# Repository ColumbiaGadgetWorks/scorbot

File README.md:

# Scorbot ER-4u ESP32 controller

A replacement controller for the Intelitek Scorbot ER-4u robot arm. An ESP32
drives the arm's six DC motors and reads its encoders and home switches. A web
UI (WiFi, with an access-point fallback) gives jogging, a live 3D view,
self-tests, homing and travel calibration, and there is a JSON HTTP/WebSocket
API.

| Folder | What's in it |
| --- | --- |
| [`hardware/scorbot-controller/`](hardware/scorbot-controller/) | KiCad 7 project for the master board, generated from Python (`generator/design.py`), autorouted, with JLCPCB fab files in `fab/` |
| [`firmware/`](firmware/) | ESP-IDF 5.3+ firmware, the single-file web UI, and host-side tests on a simulated arm |
| [`flasher/`](flasher/) | Guided web firmware installer: open <https://columbiagadgetworks.github.io/scorbot/> in Chrome or Edge and flash over USB |

The board takes an ESP32-DevKitC (WROOM-32D or -32E), six motor driver
carriers and a DROK 5 V buck module on headers. The carriers are the DRV8874
board in [`hardware/drv8874-carrier/`](hardware/drv8874-carrier/), or
Pololu's #4035 (DRV8874) or #4036 (DRV8876), picked with one menuconfig
setting in the firmware. The
robot's DB-50 cable plugs straight in. JLCPCB places the SMD parts (passives,
LEDs, the TCA9555 I/O expander and two ADS1115 ADCs); the connectors, sockets
and big capacitors are through-hole and hand-soldered.

**Status:** the board has not been ordered or tested, and the firmware has not run on
hardware. Read "Must check before ordering boards" in the
[hardware README](hardware/scorbot-controller/README.md) before ordering.

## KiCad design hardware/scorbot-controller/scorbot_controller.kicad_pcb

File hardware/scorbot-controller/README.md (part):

# Scorbot ER-4u ESP32 master board (KiCad)

KiCad project for the replacement controller: an ESP32 DevKit, six Pololu
DRV8874 carriers and a DROK mini 5 V buck module plug into a master board,
and the robot's DD-50 cable plugs straight into the board edge. JLCPCB
places the SMD parts: passives, LEDs, the SS14, the TCA9555 I/O expander and
two ADS1115 ADCs.

**Status: v0.4, generated: schematic complete, carrier and DD-50 footprints checked against their datasheets, PCB autorouted. Ready to order; check part orientation in JLC's preview.**

| File | What it is |
| --- | --- |
| `scorbot_controller.kicad_pro/.kicad_sch/.kicad_pcb` | The KiCad project (opens in KiCad 7, 8 or 9) |
| `lib/Scorbot.kicad_sym`, `lib/Scorbot.pretty/` | Custom parts: DevKit socket, DRV8874 carrier socket, DD-50 female R/A |
| `docs/schematic.pdf`, `docs/pcb_placement.png`, `docs/pcb_routed_F.png`, `docs/pcb_routed_B.png` | Previews (B side is mirrored) |
| `bom.csv` | Grouped BOM |
| `generator/design.py` | **Single source of truth**: every part, footprint, pin-to-net map and placement |
| `generate.sh` | Regenerates everything from `design.py`, then checks it |

## Regenerating

```sh
pip install kiutils cairosvg   # plus KiCad 7+ (kicad-cli and its pcbnew Python module)
# optional autorouting: Java 17+, xvfb-run and the Freerouting 1.9.0 jar
# (https://github.com/freerouting/freerouting/releases/tag/v1.9.0)
FREEROUTING_JAR=/path/freerouting-1.9.0.jar ./generate.sh
```

Routing takes about 3 minutes. `gen_route.py` retries up to `FREEROUTING_TRIES`
times (default 3) because Freerouting's result varies between runs, and it
keeps the run with the fewest unconnected items.

`generate.sh` writes the library, schematic, PCB and BOM, then:

- exports KiCad's own netlist from the schematic and checks it against
  `design.py` pin by pin (currently 354 connections, 0 mismatches);
- runs KiCad DRC on the board. Current result: 0 unconnected items, 0
  clearance or courtyard errors, and a few silkscreen and thermal-relief
  warnings. `lib_footprint_issues` only appears when the
  standard KiCad libraries aren't in the global library table.

Editing the `.kicad_sch` / `.kicad_pcb` by hand is fine once you take over
the design; just stop running the generator after that, or it overwrites your
changes.

## Must check before ordering boards

Done:

- **Pololu carrier pinout** is taken from Pololu's labeled top view: left
  row VM, GND, EN, PH, PMODE, SLEEP, VREF; right row VIN, GND, OUT1, OUT2,
  IMODE, FAULT, CS; rows 0.5" apart. Silkscreen marks VM (top left) and VIN
  (top right) on each socket: plug the carrier in components-up with its VM
  pin at the VM mark.
- **DevKit pinout** matches a photo of the board in hand (DevKitC V4 layout,
  3V3 at the antenna end).
- **Copper**: 1 oz. VIN/VM traces are 2.5 mm with 1.6/0.8 mm vias, motor
  traces 1.2 mm with 1.2/0.6 mm vias.
- **DevKit row spacing** confirmed at 1.0" (25.4 mm).
- **DD-50 footprint** follows Amphenol's D-Sub brochure for DD50S564TLF
  (stamped contacts, termination type 5): tail rows 2.54 mm apart, the row
  nearest the flange 10.40 mm from it, 2.77 mm pitch, 61.11 mm between the
  shell holes.
- **LCSC numbers** checked by search (C465732 is TI's TCA9555PWR; its LCSC
  attribute text is a generic I/O-expander template).

Still to check:

1. **DD-50 bracket holes** (not blocking): the brochure doesn't dimension
   the 50-way plastic bracket, so the two 3.2 mm holes sit on the shell-hole
   centres (61.11 mm apart), 12.94 mm behind the flange. The connector is
   held by its 50 soldered pins either way.
2. **R31-R36 LCSC number**: C341654 (Fenghua 47 R 2512 1 W, Extended;
   alternate C4347277). Confirm stock.
3. **Part orientation in JLC's placement preview** (see below). First pass
   checked: the TSSOPs were 90 degrees off and are now corrected in the CPL;
   D5 and the LEDs were already right. Re-check U5-U7 after re-uploading.
4. **Autorouted copper.** DRC-clean but not pretty; look over the VIN/VM
   and MOT paths, and the long parallel runs across the middle.
5. **Screw terminal wire entry** (J2, J3, J7) should face the board edge.
   Check in KiCad's 3D viewer.

Fit by hand, one of each pair:

- **D1 (SMBJ18A, SMB) or D8 (1.5KE18A / P6KE18A, through-hole)**: the
  reverse-polarity / over-voltage clamp. Neither is placed by JLC.
- **F1 (blade fuse holder) or J7 (screw terminal + inline fuse)**.
- **J1 (barrel jack) or J2 (screw terminal)** for the 12 V input.

## Silkscreen

`generator/gen_silk.py` runs after routing and adds front labels without
touching copper:

- **Power:** 12V IN (barrel, centre +, 18 V max), 12V IN 2 (+/-), both fuse
  options (5 A blade F1, inline-fuse terminal J7: fit one), E-STOP (NC), and
  "TVS: fit D1 OR D8".
- **Buck module:** "12V -> 5V BUCK, set to 5.0 V before fitting the ESP32",
  and each pin: IN+ 12V, IN- GND, OUT- GND, OUT+ 5V.
- **Headers:** I2C (3V3 GND SDA SCL) and GPIO from the TCA9555 (P06 P07 P17
  GND), each pin named.
- **ESP32 DevKit:** USB-end arrow; 5V, 3V3 and GND turned and moved inward,
  off the board edge and clear of the pins.
- **Driver sockets:** M1-M6 with their joints (BASE, SHOULDER, ELBOW,
  WRIST A, WRIST B, GRIPPER) inside each outline.
- **Status LEDs:** VM, 5V, STATUS, 3V3.
- **DB-50:** ROBOT CABLE / DD-50.
- **CGW logo:** 23 mm tall, bottom middle.

Edit `LABELS`, `LOGO` and `LOGO_H` in `gen_silk.py` to change them.

Logo art: `art/columbia_gadget_works_logo.png` (front, placed by
`gen_silk.py`) and `art/stealie.png` (back, `LOGO_BACK` in `gen_pcb.py`)
become filled silkscreen through `generator/silk_art.py`. Silkscreen is one
colour: every non-white area of the image prints.

## Ordering at JLCPCB

`generator/gen_fab.py` (run by `generate.sh`) writes `fab/`:

- `scorbot_controller_gerbers.zip`: upload as the PCB (2 layers, 1.6 mm,
  1 oz copper).
- `jlc_bom.csv` and `jlc_cpl.csv`: upload for PCB Assembly, top side only.
  These list only the SMD parts JLC places. Everything else is
  hand-soldered: see the buy list in the plan doc.

### Checking the JLC part numbers

For each line of `fab/jlc_bom.csv`, search the LCSC number at
<https://jlcpcb.com/parts> and confirm:

- value and package match the Comment and Footprint columns (0805, 1206,
  SMA, TSSOP-24, MSOP/VSSOP-10);
- capacitors are X7R/X5R and 25 V or more; R31-R36 are 47 R, 2512, 1 W
  (they dissipate about 0.3 W each);
- Basic vs Extended (each Extended part adds a one-off loading fee, about
  $1.50-3);
- stock covers (quantity x number of boards).

If a number is wrong or out of stock, pick any equivalent Basic part and
change it in the `LCSC` table in `generator/gen_fab.py` (or edit the CSV).

### Checking orientation in JLC's placement preview

After uploading the BOM and CPL, JLC shows each part on the board. Zoom in
and check:

- **U5 (TCA9555), U6/U7 (ADS1115)**: the pin-1 dot on the chip sits on the
  pin-1 marker of the footprint.
- **D5 (SS14)**: the cathode band is on the pad marked as cathode (toward
  the DevKit's 5 V feed).
- **LEDs D3, D4, D6, D7** (green, green, red, green): the cathode mark
  faces the GND side.
- Resistors and capacitors have no polarity.

If a part is turned the wrong way, rotate it in JLC's tool (or add 90/180 to
its Rotation in `jlc_cpl.csv`). To make the fix permanent, add the
footprint to `ROT_FIX` in `generator/gen_fab.py`. It already turns the TSSOPs
(U5-U7) by -90 degrees, because JLC's TSSOP models sit 90 degrees from KiCad's.

## Design notes

- **DB50 pinout**: SCORBOT-ER 4u User Manual, Chapter 8 (identical to the
  ER III manual Table D-1). Pins 37-44 unused; pin 22 (gripper switch) has no
  connection in the arm. Motor +/- labels differ between manuals; firmware
  sets direction.
- **Encoders**: bare IR LEDs + phototransistors. 47 R per axis from 5 V for
  VLED (ER III reference value; check against the ER-4u's upgraded PC510
  encoders). P0/P1 have 4.7 k pull-ups to 3.3 V and 1 nF, straight into the
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
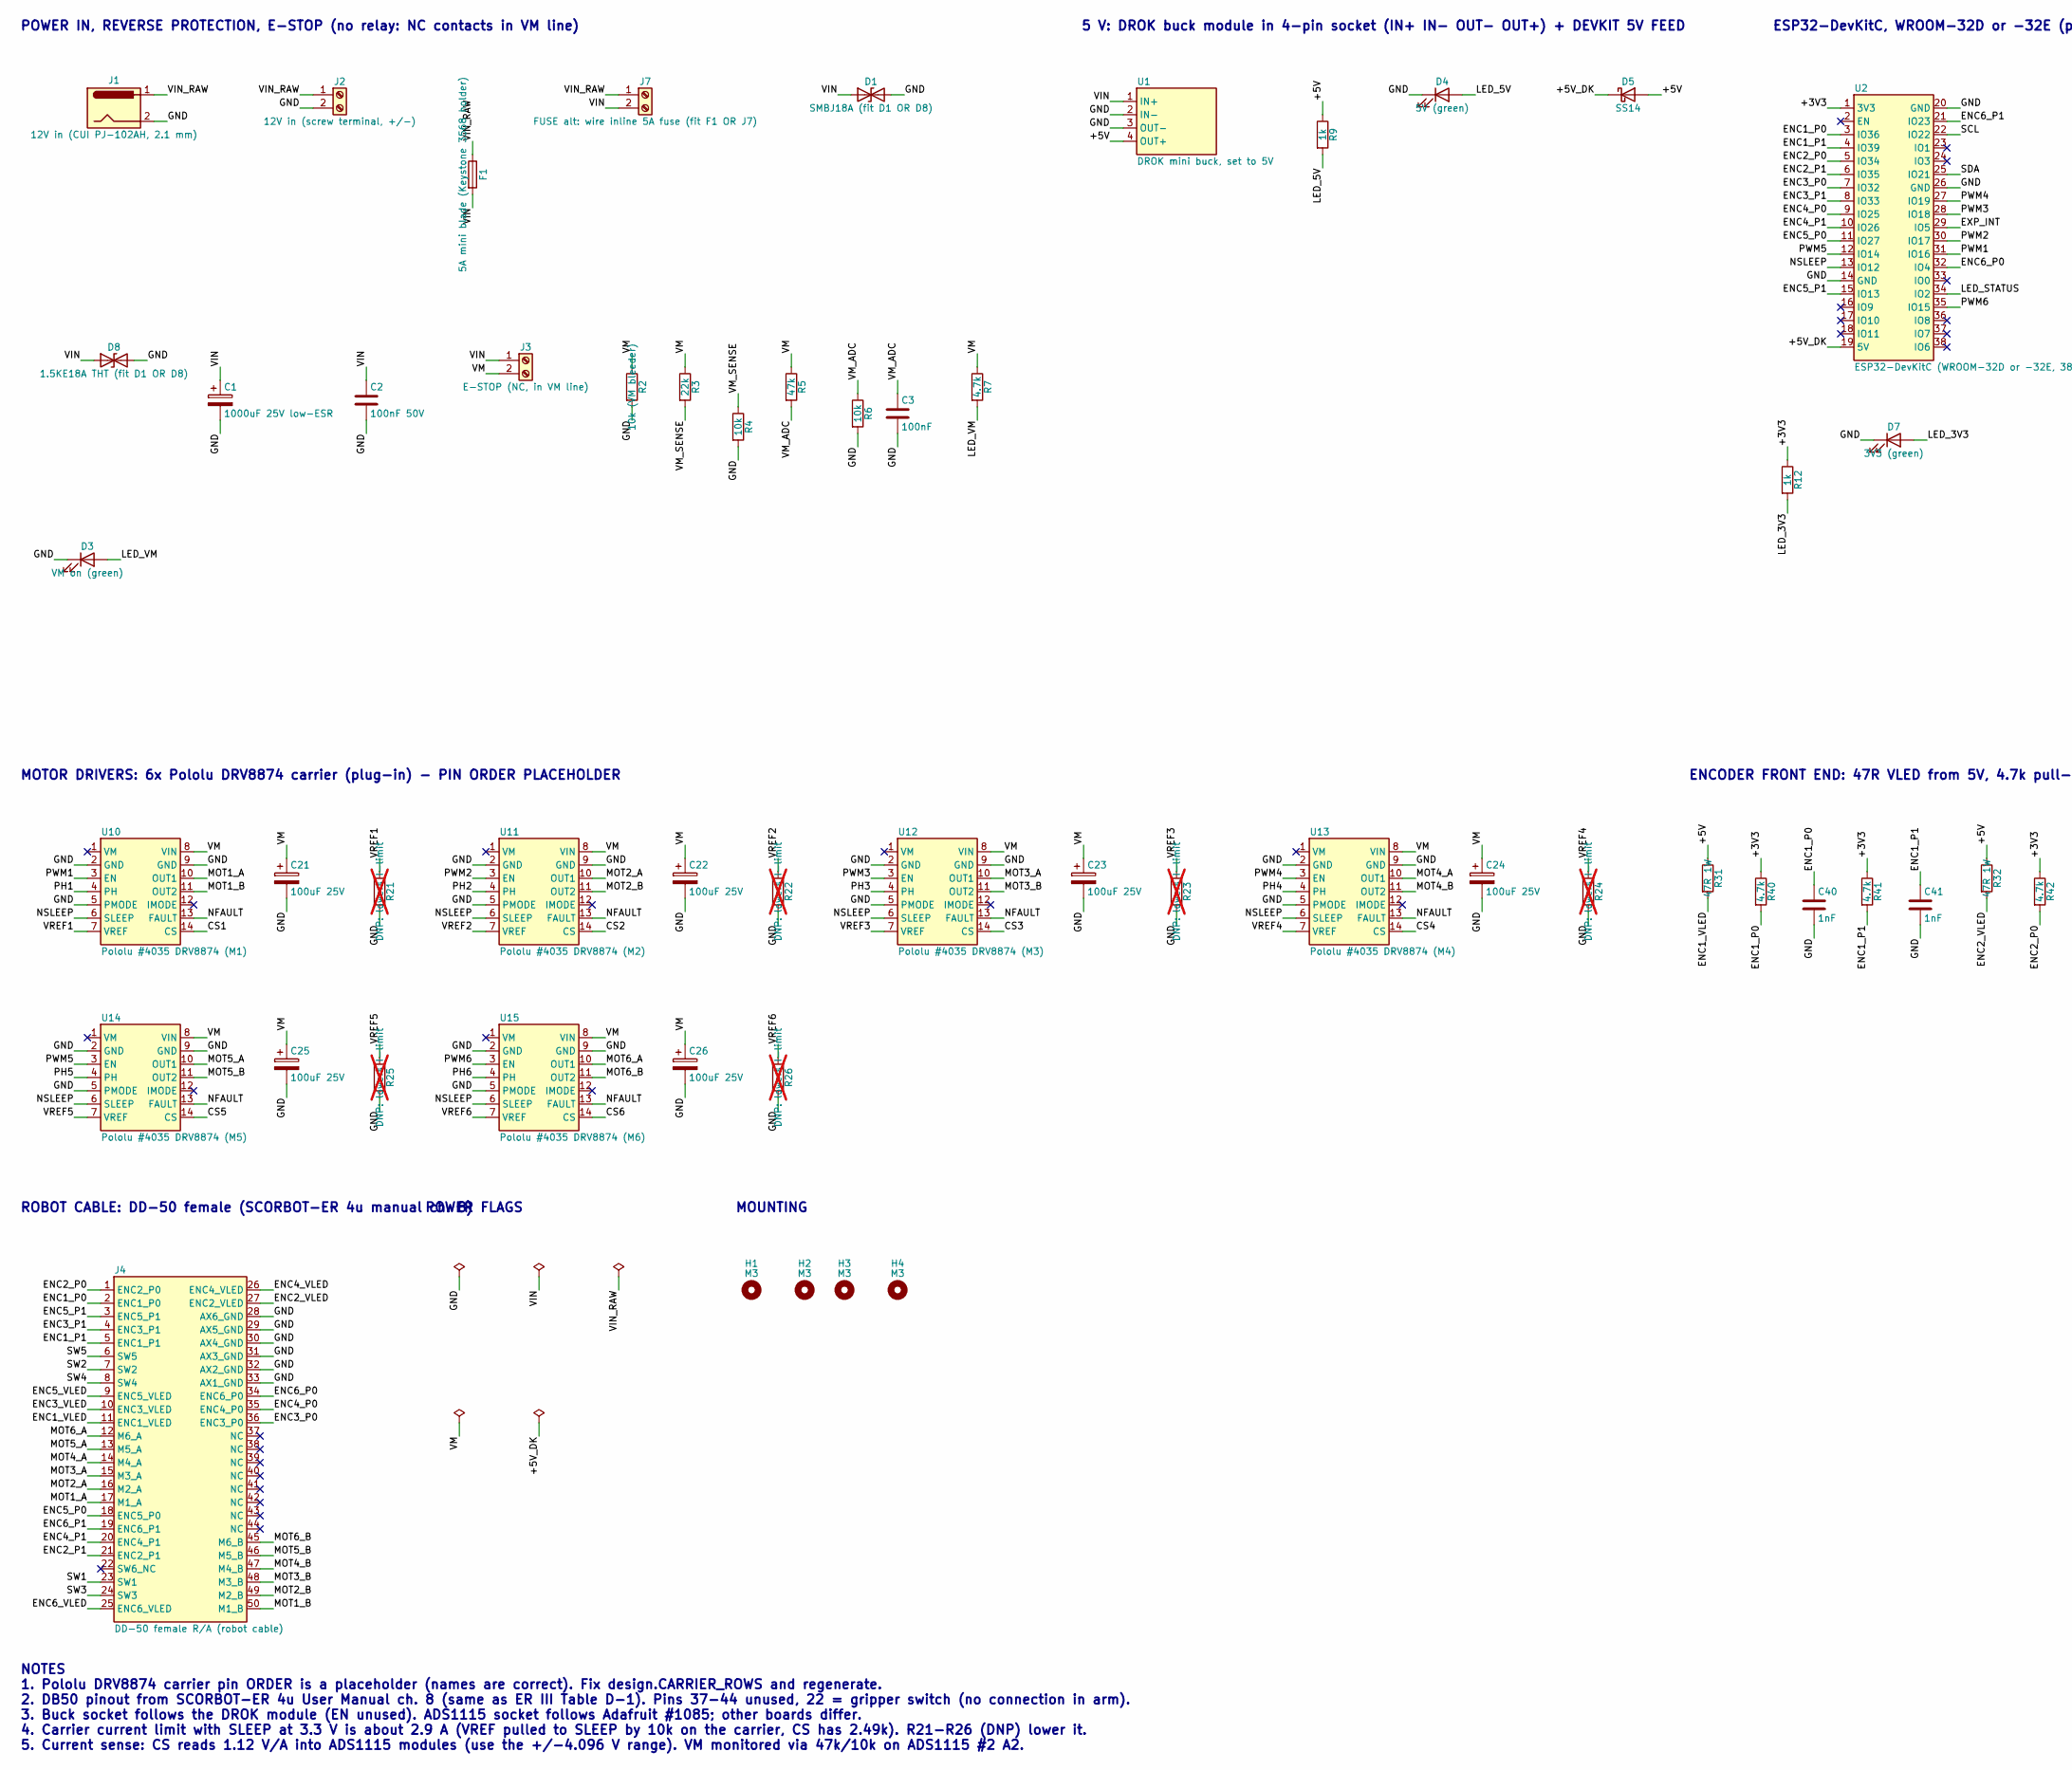
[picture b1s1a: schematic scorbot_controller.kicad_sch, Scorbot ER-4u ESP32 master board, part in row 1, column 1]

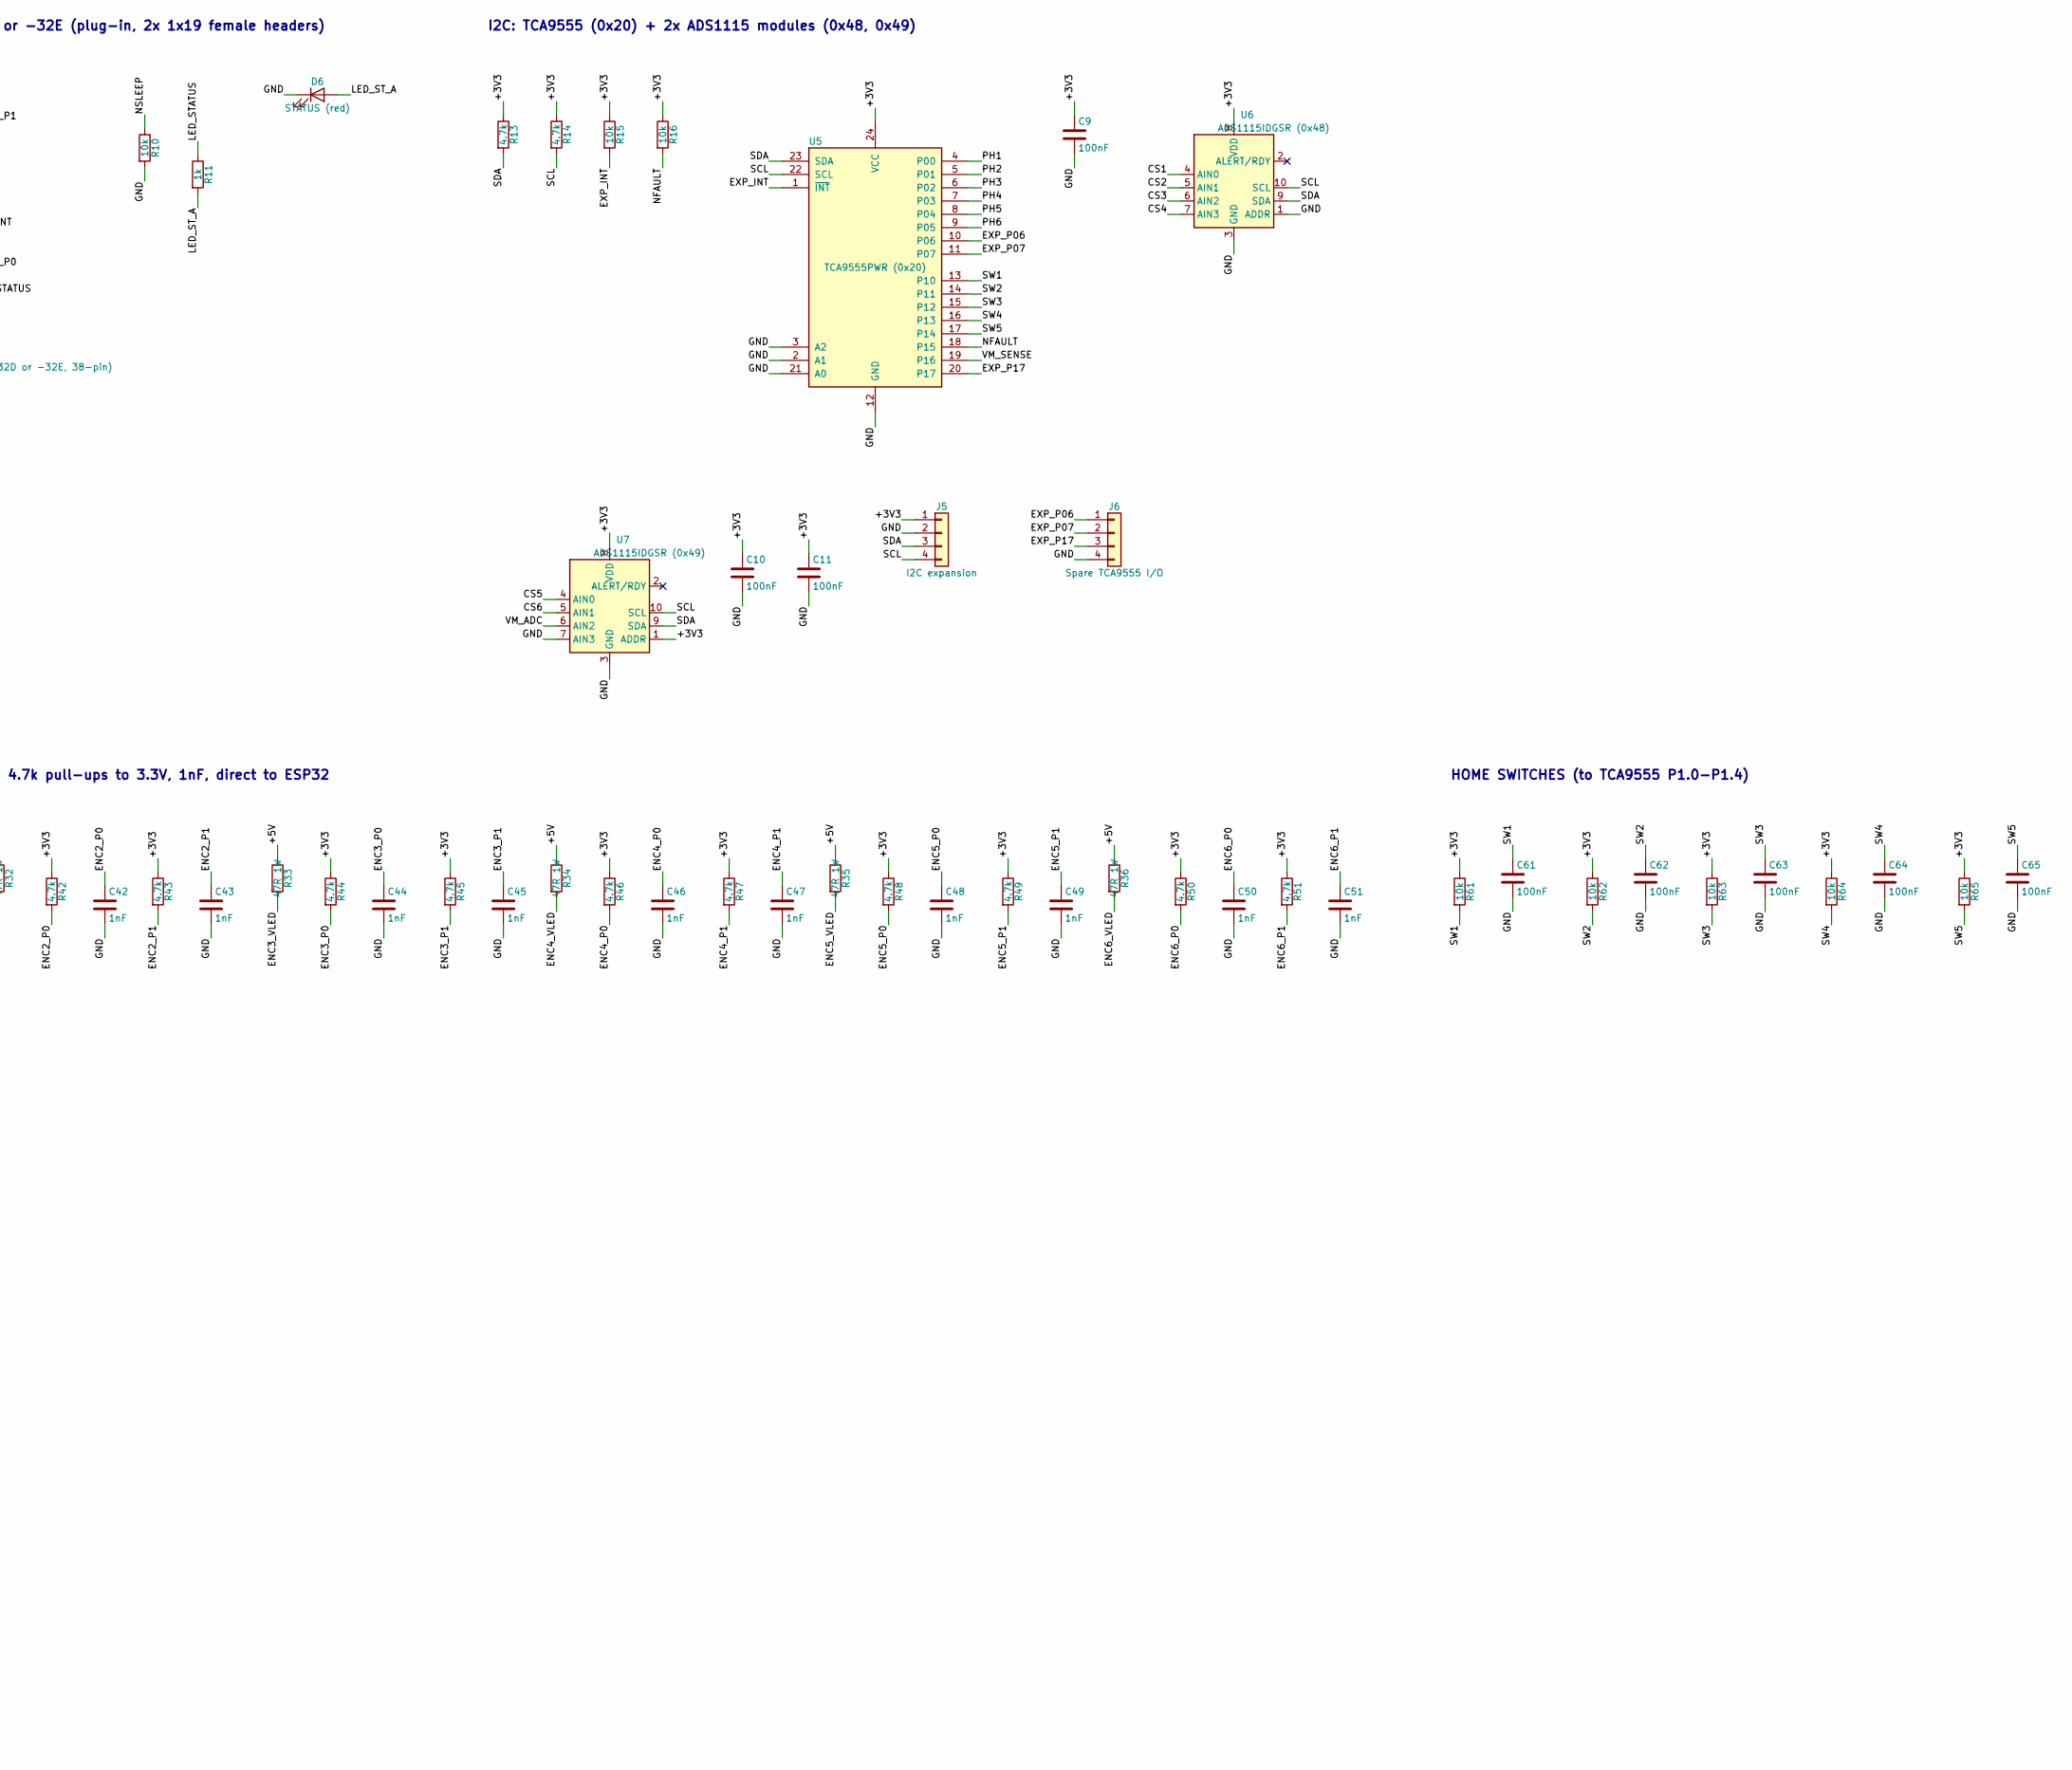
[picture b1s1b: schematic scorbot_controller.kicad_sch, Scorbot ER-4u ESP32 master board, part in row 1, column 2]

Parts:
C1: 1000uF 25V low-ESR; CP_Radial_D10.0mm_P5.00mm
C2: 100nF 50V; C_0805_2012Metric
C3, C9, C10, C11, C61, C62, C63, C64, C65: 100nF; C_0805_2012Metric
C21, C22, C23, C24, C25, C26: 100uF 25V; CP_Radial_D6.3mm_P2.50mm
C40, C41, C42, C43, C44, C45, C46, C47, C48, C49, C50, C51: 1nF; C_0805_2012Metric
D1: SMBJ18A (fit D1 OR D8); D_SMB
D3: VM on (green); LED_0805_2012Metric
D4: 5V (green); LED_0805_2012Metric
D5: SS14; D_SMA
D6: STATUS (red); LED_0805_2012Metric
D7: 3V3 (green); LED_0805_2012Metric
D8: 1.5KE18A THT (fit D1 OR D8); D_DO-201AD_P15.24mm_Horizontal
F1: 5A mini blade (Keystone 3568 holder); Fuseholder_Blade_Mini_Keystone_3568
H1, H2, H3, H4: M3; MountingHole_3.2mm_M3
J1: 12V in (CUI PJ-102AH, 2.1 mm); BarrelJack_CUI_PJ-102AH_Horizontal
J2: 12V in (screw terminal, +/-); TerminalBlock_Phoenix_MKDS-1,5-2-5.08_1x02_P5.08mm_Horizont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
J3: E-STOP (NC, in VM line); TerminalBlock_Phoenix_MKDS-1,5-2-5.08_1x02_P5.08mm_Horizont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
J4: DD-50 female R/A (robot cable); DD50_Female_Horizontal_P2.77x2.54mm_EdgePinOffset10.40mm
J5: I2C expansion; PinHeader_1x04_P2.54mm_Vertical
J6: Spare TCA9555 I/O; PinHeader_1x04_P2.54mm_Vertical
J7: FUSE alt: wire inline 5A fuse (fit F1 OR J7); TerminalBlock_Phoenix_MKDS-1,5-2-5.08_1x02_P5.08mm_Horizont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
R2: 10k (VM bleeder); R_1206_3216Metric
R3: 22k; R_0805_2012Metric
R4, R6, R10, R15, R16, R61, R62, R63, R64, R65: 10k; R_0805_2012Metric
R5: 47k; R_0805_2012Metric
R7, R13, R14, R40, R41, R42, R43, R44, R45, R46, R47, R48, R49, R50, R51: 4.7k; R_0805_2012Metric
R9, R11, R12: 1k; R_0805_2012Metric
R21, R22, R23, R24, R25, R26: DNP: lowers I-limit; R_0805_2012Metric; not fitted
R31, R32, R33, R34, R35, R36: 47R 1W; R_2512_6332Metric
U1: DROK mini buck, set to 5V; Buck_Module_4pin_Socket
U2: ESP32-DevKitC (WROOM-32D or -32E, 38-pin); ESP32_DevKitC_V4_Socket
U5: TCA9555PWR (0x20); TSSOP-24_4.4x7.8mm_P0.65mm
U6: ADS1115IDGSR (0x48); TSSOP-10_3x3mm_P0.5mm
U7: ADS1115IDGSR (0x49); TSSOP-10_3x3mm_P0.5mm
U10: Pololu #4035 DRV8874 (M1); Pololu_DRV8874_Carrier_Socket
U11: Pololu #4035 DRV8874 (M2); Pololu_DRV8874_Carrier_Socket
U12: Pololu #4035 DRV8874 (M3); Pololu_DRV8874_Carrier_Socket
U13: Pololu #4035 DRV8874 (M4); Pololu_DRV8874_Carrier_Socket
U14: Pololu #4035 DRV8874 (M5); Pololu_DRV8874_Carrier_Socket
U15: Pololu #4035 DRV8874 (M6); Pololu_DRV8874_Carrier_Socket

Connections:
+3V3: C9.1, C10.1, C11.1, J5.1, R12.1, R13.1, R14.1, R15.1, R16.1, R40.1, R41.1, R42.1, R43.1, R44.1, R45.1, R46.1, R47.1, R48.1, R49.1, R50.1, R51.1, R61.1, R62.1, R63.1, R64.1, R65.1, U2.1 (3V3), U5.24 (VCC), U6.8 (VDD), U7.1 (ADDR), U7.8 (VDD)
+5V: D5.2 (A), R9.1, R31.1, R32.1, R33.1, R34.1, R35.1, R36.1, U1.4 (OUT+)
+5V_DK: D5.1 (K), U2.19 (5V)
CS1: U6.4 (AIN0), U10.14 (CS)
CS2: U6.5 (AIN1), U11.14 (CS)
CS3: U6.6 (AIN2), U12.14 (CS)
CS4: U6.7 (AIN3), U13.14 (CS)
CS5: U7.4 (AIN0), U14.14 (CS)
CS6: U7.5 (AIN1), U15.14 (CS)
ENC1_P0: C40.1, J4.2 (ENC1_P0), R40.2, U2.3 (IO36)
ENC1_P1: C41.1, J4.5 (ENC1_P1), R41.2, U2.4 (IO39)
ENC1_VLED: J4.11 (ENC1_VLED), R31.2
ENC2_P0: C42.1, J4.1 (ENC2_P0), R42.2, U2.5 (IO34)
ENC2_P1: C43.1, J4.21 (ENC2_P1), R43.2, U2.6 (IO35)
ENC2_VLED: J4.27 (ENC2_VLED), R32.2
ENC3_P0: C44.1, J4.36 (ENC3_P0), R44.2, U2.7 (IO32)
ENC3_P1: C45.1, J4.4 (ENC3_P1), R45.2, U2.8 (IO33)
ENC3_VLED: J4.10 (ENC3_VLED), R33.2
ENC4_P0: C46.1, J4.35 (ENC4_P0), R46.2, U2.9 (IO25)
ENC4_P1: C47.1, J4.20 (ENC4_P1), R47.2, U2.10 (IO26)
ENC4_VLED: J4.26 (ENC4_VLED), R34.2
ENC5_P0: C48.1, J4.18 (ENC5_P0), R48.2, U2.11 (IO27)
ENC5_P1: C49.1, J4.3 (ENC5_P1), R49.2, U2.15 (IO13)
ENC5_VLED: J4.9 (ENC5_VLED), R35.2
ENC6_P0: C50.1, J4.34 (ENC6_P0), R50.2, U2.32 (IO4)
ENC6_P1: C51.1, J4.19 (ENC6_P1), R51.2, U2.21 (IO23)
ENC6_VLED: J4.25 (ENC6_VLED), R36.2
EXP_INT: R15.2, U2.29 (IO5), U5.1 (~INT)
EXP_P06: J6.1, U5.10 (P06)
EXP_P07: J6.2, U5.11 (P07)
EXP_P17: J6.3, U5.20 (P17)
GND: C1.2, C2.2, C3.2, C9.2, C10.2, C11.2, C21.2, C22.2, C23.2, C24.2, C25.2, C26.2, C40.2, C41.2, C42.2, C43.2, C44.2, C45.2, C46.2, C47.2, C48.2, C49.2, C50.2, C51.2, C61.2, C62.2, C63.2, C64.2, C65.2, D1.2 (A2), D3.1 (K), D4.1 (K), D6.1 (K), D7.1 (K), D8.2 (A2), J1.2, J2.2, J4.28 (AX6_GND), J4.29 (AX5_GND), J4.30 (AX4_GND), J4.31 (AX3_GND), J4.32 (AX2_GND), J4.33 (AX1_GND), J5.2, J6.4, R2.2, R4.2, R6.2, R10.2, R21.2, R22.2, R23.2, R24.2, R25.2, R26.2, U1.2 (IN-), U1.3 (OUT-), U2.14 (GND), U2.20 (GND), U2.26 (GND), U5.2 (A1), U5.3 (A2), U5.12 (GND), U5.21 (A0), U6.1 (ADDR), U6.3 (GND), U7.3 (GND), U7.7 (AIN3), U10.2 (GND), U10.5 (PMODE), U10.9 (GND), U11.2 (GND), U11.5 (PMODE), U11.9 (GND), U12.2 (GND), U12.5 (PMODE), U12.9 (GND), U13.2 (GND), U13.5 (PMODE), U13.9 (GND)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
LED_3V3: D7.2 (A), R12.2
LED_5V: D4.2 (A), R9.2
LED_STATUS: R11.1, U2.34 (IO2)
LED_ST_A: D6.2 (A), R11.2
LED_VM: D3.2 (A), R7.2
MOT1_A: J4.17 (M1_A), U10.10 (OUT1)
MOT1_B: J4.50 (M1_B), U10.11 (OUT2)
MOT2_A: J4.16 (M2_A), U11.10 (OUT1)
MOT2_B: J4.49 (M2_B), U11.11 (OUT2)
MOT3_A: J4.15 (M3_A), U12.10 (OUT1)
MOT3_B: J4.48 (M3_B), U12.11 (OUT2)
MOT4_A: J4.14 (M4_A), U13.10 (OUT1)
MOT4_B: J4.47 (M4_B), U13.11 (OUT2)
MOT5_A: J4.13 (M5_A), U14.10 (OUT1)
MOT5_B: J4.46 (M5_B), U14.11 (OUT2)
MOT6_A: J4.12 (M6_A), U15.10 (OUT1)
MOT6_B: J4.45 (M6_B), U15.11 (OUT2)
NFAULT: R16.2, U5.18 (P15), U10.13 (FAULT), U11.13 (FAULT), U12.13 (FAULT), U13.13 (FAULT), U14.13 (FAULT), U15.13 (FAULT)
NSLEEP: R10.1, U2.13 (IO12), U10.6 (SLEEP), U11.6 (SLEEP), U12.6 (SLEEP), U13.6 (SLEEP), U14.6 (SLEEP), U15.6 (SLEEP)
PH1: U5.4 (P00), U10.4 (PH)
PH2: U5.5 (P01), U11.4 (PH)
PH3: U5.6 (P02), U12.4 (PH)
PH4: U5.7 (P03), U13.4 (PH)
PH5: U5.8 (P04), U14.4 (PH)
PH6: U5.9 (P05), U15.4 (PH)
PWM1: U2.31 (IO16), U10.3 (EN)
PWM2: U2.30 (IO17), U11.3 (EN)
PWM3: U2.28 (IO18), U12.3 (EN)
PWM4: U2.27 (IO19), U13.3 (EN)
PWM5: U2.12 (IO14), U14.3 (EN)
PWM6: U2.35 (IO15), U15.3 (EN)
SCL: J5.4, R14.2, U2.22 (IO22), U5.22 (SCL), U6.10 (SCL), U7.10 (SCL)
SDA: J5.3, R13.2, U2.25 (IO21), U5.23 (SDA), U6.9 (SDA), U7.9 (SDA)
SW1: C61.1, J4.23 (SW1), R61.2, U5.13 (P10)
SW2: C62.1, J4.7 (SW2), R62.2, U5.14 (P11)
SW3: C63.1, J4.24 (SW3), R63.2, U5.15 (P12)
SW4: C64.1, J4.8 (SW4), R64.2, U5.16 (P13)
SW5: C65.1, J4.6 (SW5), R65.2, U5.17 (P14)
VIN: C1.1, C2.1, D1.1 (A1), D8.1 (A1), F1.2, J3.1, J7.2, U1.1 (IN+)
VIN_RAW: F1.1, J1.1, J2.1, J7.1
VM: C21.1, C22.1, C23.1, C24.1, C25.1, C26.1, J3.2, R2.1, R3.1, R5.1, R7.1, U10.8 (VIN), U11.8 (VIN), U12.8 (VIN), U13.8 (VIN), U14.8 (VIN), U15.8 (VIN)
VM_ADC: C3.1, R5.2, R6.1, U7.6 (AIN2)
VM_SENSE: R3.2, R4.1, U5.19 (P16)
VREF1: R21.1, U10.7 (VREF)
VREF2: R22.1, U11.7 (VREF)
VREF3: R23.1, U12.7 (VREF)
VREF4: R24.1, U13.7 (VREF)
VREF5: R25.1, U14.7 (VREF)
VREF6: R26.1, U15.7 (VREF)

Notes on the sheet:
POWER IN, REVERSE PROTECTION, E-STOP (no relay: NC contacts in VM line)
5 V: DROK buck module in 4-pin socket (IN+ IN- OUT- OUT+) + DEVKIT 5V FEED
ESP32-DevKitC, WROOM-32D or -32E (plug-in, 2x 1x19 female headers)
I2C: TCA9555 (0x20) + 2x ADS1115 modules (0x48, 0x49)
MOTOR DRIVERS: 6x Pololu DRV8874 carrier (plug-in) - PIN ORDER PLACEHOLDER
ENCODER FRONT END: 47R VLED from 5V, 4.7k pull-ups to 3.3V, 1nF, direct to ESP32
HOME SWITCHES (to TCA9555 P1.0-P1.4)
ROBOT CABLE: DD-50 female (SCORBOT-ER 4u manual ch. 8)
POWER FLAGS
MOUNTING
NOTES 1. Pololu DRV8874 carrier pin ORDER is a placeholder (names are correct). Fix design.CARRIER_ROWS and regenerate. 2. DB50 pinout from SCORBOT-ER 4u User Manual ch. 8 (same as ER III Table D-1). Pins 37-44 unused, 22 = gripper switch (no connection in arm). 3. Buck socket follows the DROK modu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

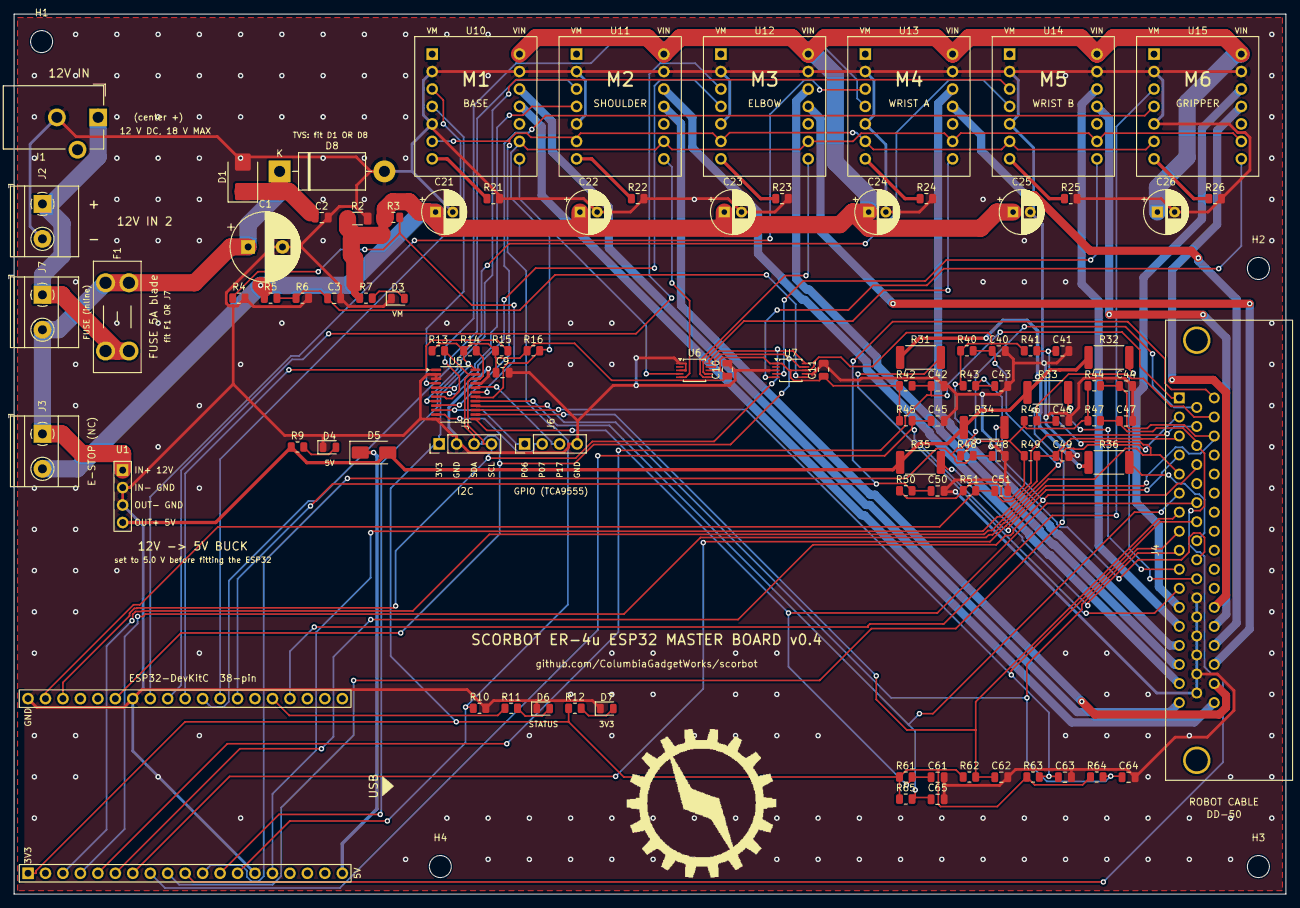
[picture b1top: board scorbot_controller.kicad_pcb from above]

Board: 2 copper layers, 185.0 x 128.0 mm, 102 parts (0 on the bottom side), 81 nets.

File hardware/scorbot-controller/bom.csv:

Qty,Value,Footprint,References,Populate
1,"12V in (CUI PJ-102AH, 2.1 mm)",Connector_BarrelJack:BarrelJack_CUI_PJ-102AH_Horizontal,J1,yes
1,"12V in (screw terminal, +/-)","TerminalBlock_Phoenix:TerminalBlock_Phoenix_MKDS-1,5-2-5.08_1x02_P5.08mm_Horizontal",J2,yes
1,5A mini blade (Keystone 3568 holder),Fuse:Fuseholder_Blade_Mini_Keystone_3568,F1,yes
1,FUSE alt: wire inline 5A fuse (fit F1 OR J7),"TerminalBlock_Phoenix:TerminalBlock_Phoenix_MKDS-1,5-2-5.08_1x02_P5.08mm_Horizontal",J7,yes
1,SMBJ18A (fit D1 OR D8),Diode_SMD:D_SMB,D1,yes
1,1.5KE18A THT (fit D1 OR D8),Diode_THT:D_DO-201AD_P15.24mm_Horizontal,D8,yes
1,1000uF 25V low-ESR,Capacitor_THT:CP_Radial_D10.0mm_P5.00mm,C1,yes
1,100nF 50V,Capacitor_SMD:C_0805_2012Metric,C2,yes
1,"E-STOP (NC, in VM line)","TerminalBlock_Phoenix:TerminalBlock_Phoenix_MKDS-1,5-2-5.08_1x02_P5.08mm_Horizontal",J3,yes
1,10k (VM bleeder),Resistor_SMD:R_1206_3216Metric,R2,yes
1,22k,Resistor_SMD:R_0805_2012Metric,R3,yes
10,10k,Resistor_SMD:R_0805_2012Metric,R4 R6 R10 R15 R16 R61 R62 R63 R64 R65,yes
1,47k,Resistor_SMD:R_0805_2012Metric,R5,yes
9,100nF,Capacitor_SMD:C_0805_2012Metric,C3 C9 C10 C11 C61 C62 C63 C64 C65,yes
15,4.7k,Resistor_SMD:R_0805_2012Metric,R7 R13 R14 R40 R41 R42 R43 R44 R45 R46 R47 R48 R49 R50 R51,yes
1,VM on (green),LED_SMD:LED_0805_2012Metric,D3,yes
1,"DROK mini buck, set to 5V",Scorbot:Buck_Module_4pin_Socket,U1,yes
3,1k,Resistor_SMD:R_0805_2012Metric,R9 R11 R12,yes
1,5V (green),LED_SMD:LED_0805_2012Metric,D4,yes
1,SS14,Diode_SMD:D_SMA,D5,yes
1,"ESP32-DevKitC (WROOM-32D or -32E, 38-pin)",Scorbot:ESP32_DevKitC_V4_Socket,U2,yes
1,STATUS (red),LED_SMD:LED_0805_2012Metric,D6,yes
1,3V3 (green),LED_SMD:LED_0805_2012Metric,D7,yes
1,TCA9555PWR (0x20),Package_SO:TSSOP-24_4.4x7.8mm_P0.65mm,U5,yes
1,ADS1115IDGSR (0x48),Package_SO:TSSOP-10_3x3mm_P0.5mm,U6,yes
1,ADS1115IDGSR (0x49),Package_SO:TSSOP-10_3x3mm_P0.5mm,U7,yes
1,I2C expansion,Connector_PinHeader_2.54mm:PinHeader_1x04_P2.54mm_Vertical,J5,yes
1,Spare TCA9555 I/O,Connector_PinHeader_2.54mm:PinHeader_1x04_P2.54mm_Vertical,J6,yes
1,Pololu #4035 DRV8874 (M1),Scorbot:Pololu_DRV8874_Carrier_Socket,U10,yes
6,100uF 25V,Capacitor_THT:CP_Radial_D6.3mm_P2.50mm,C21 C22 C23 C24 C25 C26,yes
6,DNP: lowers I-limit,Resistor_SMD:R_0805_2012Metric,R21 R22 R23 R24 R25 R26,DNP
1,Pololu #4035 DRV8874 (M2),Scorbot:Pololu_DRV8874_Carrier_Socket,U11,yes
1,Pololu #4035 DRV8874 (M3),Scorbot:Pololu_DRV8874_Carrier_Socket,U12,yes
1,Pololu #4035 DRV8874 (M4),Scorbot:Pololu_DRV8874_Carrier_Socket,U13,yes
1,Pololu #4035 DRV8874 (M5),Scorbot:Pololu_DRV8874_Carrier_Socket,U14,yes
1,Pololu #4035 DRV8874 (M6),Scorbot:Pololu_DRV8874_Carrier_Socket,U15,yes
6,47R 1W,Resistor_SMD:R_2512_6332Metric,R31 R32 R33 R34 R35 R36,yes
12,1nF,Capacitor_SMD:C_0805_2012Metric,C40 C41 C42 C43 C44 C45 C46 C47 C48 C49 C50 C51,yes
1,DD-50 female R/A (robot cable),Scorbot:DD50_Female_Horizontal_P2.77x2.54mm_EdgePinOffset10.40mm,J4,yes
4,M3,MountingHole:MountingHole_3.2mm_M3,H1 H2 H3 H4,yes

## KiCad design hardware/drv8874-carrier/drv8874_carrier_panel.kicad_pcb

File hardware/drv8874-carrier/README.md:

# DRV8874 carrier (Pololu #4035 clone)

A small board with TI's DRV8874 that plugs into the master board's motor
driver sockets in place of a Pololu #4035. It has the same 0.6" x 0.7" size,
the same 2x7 pinout and the same default resistor values, so the master board
and the firmware's DRV8874 settings work with either. JLC places every SMD
part; you solder the 0.1" pins.

## Files

| Path | What it is |
|---|---|
| `generator/gen_board.py` | Builds and routes `drv8874_carrier.kicad_pcb` (version A), then makes `drv8874_carrier_b.kicad_pcb` (version B). Needs `FREEROUTING_JAR` |
| `generator/gen_fab.py` | Makes a 3x2 panel of each version (`*_panel.kicad_pcb`) and the JLC files |
| `fab/b/panel/` | **Order this:** gerbers zip, `jlc_bom.csv`, `jlc_cpl.csv` for the version B panel |
| `fab/a/panel/` | The same for version A |
| `fab/<a or b>/single/` | One board, if you would rather let JLC panelize |
| `fab/b/rfq/` | RFQ package for any assembler: `drv8874_carrier_b_rfq.zip` holds panel and single gerbers, a complete BOM with manufacturer part numbers, CPLs (mm from the lower-left corner) and `RFQ_NOTES.txt`. Made by `generator/gen_rfq.py` |
| `docs/` | Renders: `version_a.png`, `version_b.png` (front, and back as seen from below), `panel_b.png` |

## Two versions

Both have the same parts, placement and routing; B adds copper.

- **A:** VM, OUT1 and OUT2 are 1.0-1.2 mm traces. The thermal pad has six
  vias around the paste area.
- **B (recommended), closer to Pololu's board:** VM, OUT1 and OUT2 also get
  copper pours that fill the free space around their traces (on whichever
  layer each runs), and the thermal pad has 15 vias (a 5 x 3 grid) into the
  bottom GND pour. The middle row of vias sits in the pad's solder area, as
  on Pololu's board; a little solder wicks down them, which is normal.

```
cd generator
FREEROUTING_JAR=/path/freerouting-1.9.0.jar python3 gen_board.py
python3 gen_fab.py
```

## Circuit

It follows Pololu's DRV887x carrier schematic, with two changes:

- **No reverse-voltage MOSFET.** The master board already has reverse-polarity
  protection, so VIN and VM are tied together on the carrier. Don't use this
  carrier on its own without other protection.
- **VCP uses 100 nF** (TI's recommended value; Pololu fits 220 nF).
- **JLC Basic parts wherever possible**, so the DRV8874 is the only Extended
  part: 10 uF 25 V 0805 bulk capacitors (Pololu uses 4.7 uF), a 0402 22 nF
  charge-pump capacitor, and **2.4 k on CS instead of 2.49 k**. CS therefore
  reads 1.08 V/A (Pololu: 1.12) and the current limit is about 3.1 A (Pololu:
  about 2.9 A). The firmware's default driver setting matches this board.

| Ref | Part | LCSC | Notes |
|---|---|---|---|
| U1 | DRV8874PWPR (HTSSOP-16) | C1855818 | Extended part |
| C1, C2 | 10 uF 25 V X5R 0805 | C15850 | VM bulk |
| C3, C4 | 100 nF 50 V 0603 | C14663 | VM bypass (C3 by the VM pin, C4 by the VM header pin) |
| C5 | 22 nF 50 V X7R 0402 | C1532 | Charge-pump flying cap (CPH-CPL) |
| C6 | 100 nF 50 V 0603 | C14663 | VCP to VM |
| R2 | 10 k 0603 | C25804 | VREF pulled to SLEEP, as on Pololu's board |
| R3 | 2.4 k 1% 0603 | C22940 | CS (IPROPI) to GND: 1.08 V/A, about 3.1 A limit at VREF = 3.3 V |
| R4 | 20 k 0603 | C4184 | IMODE to GND, as on Pololu's board |

PMODE is left floating on the carrier, as on Pololu's board; the master
board ties it to GND (PH/EN mode).

**Pins**, top view, top to bottom:

| Left | Right |
|---|---|
| VM | VIN (tied to VM) |
| GND (square pad) | GND (square pad) |
| EN | OUT1 |
| PH | OUT2 |
| PMODE | IMODE |
| SLEEP | FAULT |
| VREF | CS |

The back has the pin names, like Pololu's.

## Layout

- 2 layers, 1.6 mm, 1 oz.
- VM, OUT1 and OUT2 are drawn by hand at 1.0-1.2 mm and locked; the
  autorouter does the rest. They neck down to 0.4 mm only for the last
  millimetre into the 0.65 mm-pitch chip pins.
- The chip's thermal pad has 0.3 mm vias to the bottom GND pour (6 in A,
  15 in B), and a solder-mask-defined opening so the paste stays on the pad.
- GND is poured on both layers.

## Ordering at JLCPCB

All three files are also in `fab/JLC_upload_6up_version_b/`, numbered in
upload order (`fab/JLC_upload_single_version_b/` has the single-board set). Use these, not the `fab/b/rfq/` files: the RFQ BOM lists
per-board designators and its CPL is not in JLC's column format.

1. Upload `fab/b/panel/drv8874_carrier_b_panel_gerbers.zip`.
2. PCB options:
   - Layers 2, thickness 1.6 mm, 1 oz.
   - **Panel by Customer**, panel format 3 x 2 (6 boards per panel). The
     straight lines across the panel on the outline layer are V-cuts; say so
     in the order remark ("V-cut along all internal straight lines").
   - Edge rails: none (the panel already has 5 mm rails with fiducials and
     1.152 mm tooling holes).
   - Quantity 5 panels (the minimum).
3. Assembly: Economic, top side, **PCBA quantity 2 panels** (12 boards).
   Upload `fab/b/panel/jlc_bom.csv` and `fab/b/panel/jlc_cpl.csv`.
4. Check the placement preview:
   - **U1**: the pin-1 dot on the chip goes at the bottom-left, by the small
     triangle on the silkscreen (pins 1-8 run along the bottom edge). I've
     applied the same 90-degree correction that the master board's TSSOPs
     needed; if the chip's leads cross the pads, rotate it by 90 degrees.
   - Capacitors and resistors have no polarity.
5. Consider "Confirm Parts Placement: Yes".

To let JLC panelize instead, use the `fab/b/single/` files and choose "Panel by
JLCPCB" (check that JLC offers assembly with that option for your order).

## After assembly

- Solder two 1x7 male 0.1" headers, long pins down, components up.
- Firmware: the default build is set for this carrier (CS 1.08 V/A, 2.5 A
  software trip). See `firmware/README.md`.
- First power-up: one carrier, motor disconnected, current-limited bench
  supply at 12 V. Check that VM draws a few mA, then try a motor from the
  web UI's motor test.

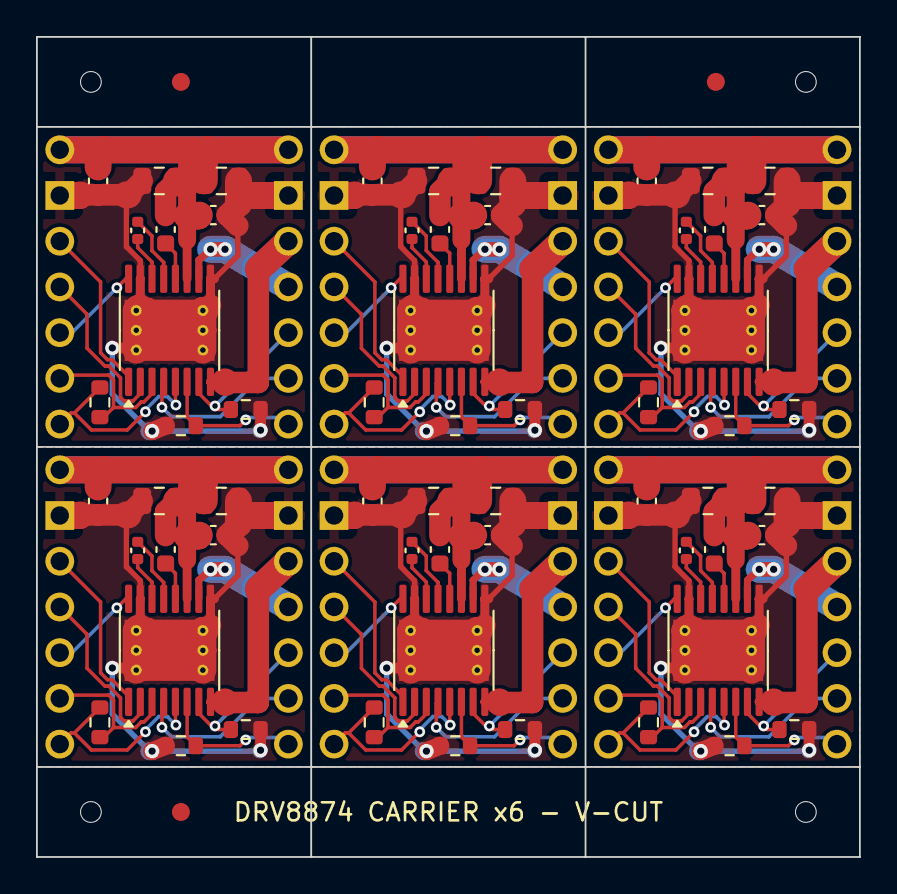
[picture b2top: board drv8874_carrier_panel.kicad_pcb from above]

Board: 2 copper layers, 45.7 x 45.6 mm, 79 parts (0 on the bottom side), 15 nets.

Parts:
C1_1, C1_2, C1_3, C1_4, C1_5, C1_6, C2_1, C2_2, C2_3, C2_4, C2_5, C2_6: 10uF 25V; C_0805_2012Metric
C3_1, C3_2, C3_3, C3_4, C3_5, C3_6, C4_1, C4_2, C4_3, C4_4, C4_5, C4_6, C6_1, C6_2, C6_3, C6_4, C6_5, C6_6: 100nF 50V; C_0603_1608Metric
C5_1, C5_2, C5_3, C5_4, C5_5, C5_6: 22nF 50V; C_0402_1005Metric
FID1, FID2, FID3: Fiducial_1mm_Mask2mm
H1, H2, H3, H4: (no value)
J1_1, J1_2, J1_3, J1_4, J1_5, J1_6, J2_1, J2_2, J2_3, J2_4, J2_5, J2_6: 1x7 0.1in pins (hand-soldered); PinHeader_1x07_P2.54mm_Vertical
R2_1, R2_2, R2_3, R2_4, R2_5, R2_6: 10k; R_0603_1608Metric
R3_1, R3_2, R3_3, R3_4, R3_5, R3_6: 2.4k 1%; R_0603_1608Metric
R4_1, R4_2, R4_3, R4_4, R4_5, R4_6: 20k; R_0603_1608Metric
U1_1, U1_2, U1_3, U1_4, U1_5, U1_6: DRV8874PWPR; HTSSOP-16-1EP_4.4x5mm_P0.65mm_EP3.4x5mm_Mask2.46x2.31mm

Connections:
CPH: C5_1.2, C5_2.2, C5_3.2, C5_4.2, C5_5.2, C5_6.2, U1_1.13, U1_2.13, U1_3.13, U1_4.13, U1_5.13, U1_6.13
CPL: C5_1.1, C5_2.1, C5_3.1, C5_4.1, C5_5.1, C5_6.1, U1_1.14, U1_2.14, U1_3.14, U1_4.14, U1_5.14, U1_6.14
CS: J2_1.7, J2_2.7, J2_3.7, J2_4.7, J2_5.7, J2_6.7, R3_1.2, R3_2.2, R3_3.2, R3_4.2, R3_5.2, R3_6.2, U1_1.6, U1_2.6, U1_3.6, U1_4.6, U1_5.6, U1_6.6
EN: J1_1.3, J1_2.3, J1_3.3, J1_4.3, J1_5.3, J1_6.3, U1_1.1, U1_2.1, U1_3.1, U1_4.1, U1_5.1, U1_6.1
FAULT: J2_1.6, J2_2.6, J2_3.6, J2_4.6, J2_5.6, J2_6.6, U1_1.4, U1_2.4, U1_3.4, U1_4.4, U1_5.4, U1_6.4
GND: C1_1.1, C1_2.1, C1_3.1, C1_4.1, C1_5.1, C1_6.1, C2_1.2, C2_2.2, C2_3.2, C2_4.2, C2_5.2, C2_6.2, C3_1.2, C3_2.2, C3_3.2, C3_4.2, C3_5.2, C3_6.2, C4_1.1, C4_2.1, C4_3.1, C4_4.1, C4_5.1, C4_6.1, J1_1.2, J1_2.2, J1_3.2, J1_4.2, J1_5.2, J1_6.2, J2_1.2, J2_2.2, J2_3.2, J2_4.2, J2_5.2, J2_6.2, R3_1.1, R3_2.1, R3_3.1, R3_4.1, R3_5.1, R3_6.1, R4_1.2, R4_2.2, R4_3.2, R4_4.2, R4_5.2, R4_6.2, U1_1.9, U1_1.15, U1_1.17, U1_2.9, U1_2.15, U1_2.17, U1_3.9, U1_3.15, U1_3.17, U1_4.9, U1_4.15, U1_4.17, U1_5.9, U1_5.15, U1_5.17, U1_6.9, U1_6.15, U1_6.17
IMODE: J2_1.5, J2_2.5, J2_3.5, J2_4.5, J2_5.5, J2_6.5, R4_1.1, R4_2.1, R4_3.1, R4_4.1, R4_5.1, R4_6.1, U1_1.7, U1_2.7, U1_3.7, U1_4.7, U1_5.7, U1_6.7
OUT1: J2_1.3, J2_2.3, J2_3.3, J2_4.3, J2_5.3, J2_6.3, U1_1.8, U1_2.8, U1_3.8, U1_4.8, U1_5.8, U1_6.8
OUT2: J2_1.4, J2_2.4, J2_3.4, J2_4.4, J2_5.4, J2_6.4, U1_1.10, U1_2.10, U1_3.10, U1_4.10, U1_5.10, U1_6.10
PH: J1_1.4, J1_2.4, J1_3.4, J1_4.4, J1_5.4, J1_6.4, U1_1.2, U1_2.2, U1_3.2, U1_4.2, U1_5.2, U1_6.2
PMODE: J1_1.5, J1_2.5, J1_3.5, J1_4.5, J1_5.5, J1_6.5, U1_1.16, U1_2.16, U1_3.16, U1_4.16, U1_5.16, U1_6.16
SLEEP: J1_1.6, J1_2.6, J1_3.6, J1_4.6, J1_5.6, J1_6.6, R2_1.1, R2_2.1, R2_3.1, R2_4.1, R2_5.1, R2_6.1, U1_1.3, U1_2.3, U1_3.3, U1_4.3, U1_5.3, U1_6.3
VCP: C6_1.1, C6_2.1, C6_3.1, C6_4.1, C6_5.1, C6_6.1, U1_1.12, U1_2.12, U1_3.12, U1_4.12, U1_5.12, U1_6.12
VM: C1_1.2, C1_2.2, C1_3.2, C1_4.2, C1_5.2, C1_6.2, C2_1.1, C2_2.1, C2_3.1, C2_4.1, C2_5.1, C2_6.1, C3_1.1, C3_2.1, C3_3.1, C3_4.1, C3_5.1, C3_6.1, C4_1.2, C4_2.2, C4_3.2, C4_4.2, C4_5.2, C4_6.2, C6_1.2, C6_2.2, C6_3.2, C6_4.2, C6_5.2, C6_6.2, J1_1.1, J1_2.1, J1_3.1, J1_4.1, J1_5.1, J1_6.1, J2_1.1, J2_2.1, J2_3.1, J2_4.1, J2_5.1, J2_6.1, U1_1.11, U1_2.11, U1_3.11, U1_4.11, U1_5.11, U1_6.11
VREF: J1_1.7, J1_2.7, J1_3.7, J1_4.7, J1_5.7, J1_6.7, R2_1.2, R2_2.2, R2_3.2, R2_4.2, R2_5.2, R2_6.2, U1_1.5, U1_2.5, U1_3.5, U1_4.5, U1_5.5, U1_6.5
